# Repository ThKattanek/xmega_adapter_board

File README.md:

# XMEGA Adapter Board (ATXMEGA256D3)
Eine Adapter Platine für den XMEGA, um ihn auf dem Steckbrett zu nutzen.

### <font color="red"> Vorsicht! Revision 1.2.1 noch nicht fertigen lassen, bis ich die ersten Platinen getestet habe! </font>

## Fotos

## Anschluss und Programmiergerät

Das Board muss an VCC und AVCC mit 3,3V verbunden werden sowie GND mit Masse.  Ich verwende als Programmieragerät den AVR Programmer von Diamex. (Atmel AVRISP MKII kompatibel)
[https://www.diamex.de/dxshop/Diamex-AVR-Prog-Programmer-fuer-ISP-PDI-TPI](https://www.diamex.de/dxshop/Diamex-AVR-Prog-Programmer-fuer-ISP-PDI-TPI)  
Der XMEGA wird lediglich über 2 Leitungen mit den Programmiergerät verbunden. (PDI_CLK und PDI_DATA) Die Kommunikation erfolgt über PDI.

## Erste Schritte mit AVRDUDE und den XMEGA
### 1. avrdude -c avrispmkII -p x256d3 
Wenn alles richtig angeschlossen wurde sollte als Device ID 0x1e9844 ausgegeben werden.

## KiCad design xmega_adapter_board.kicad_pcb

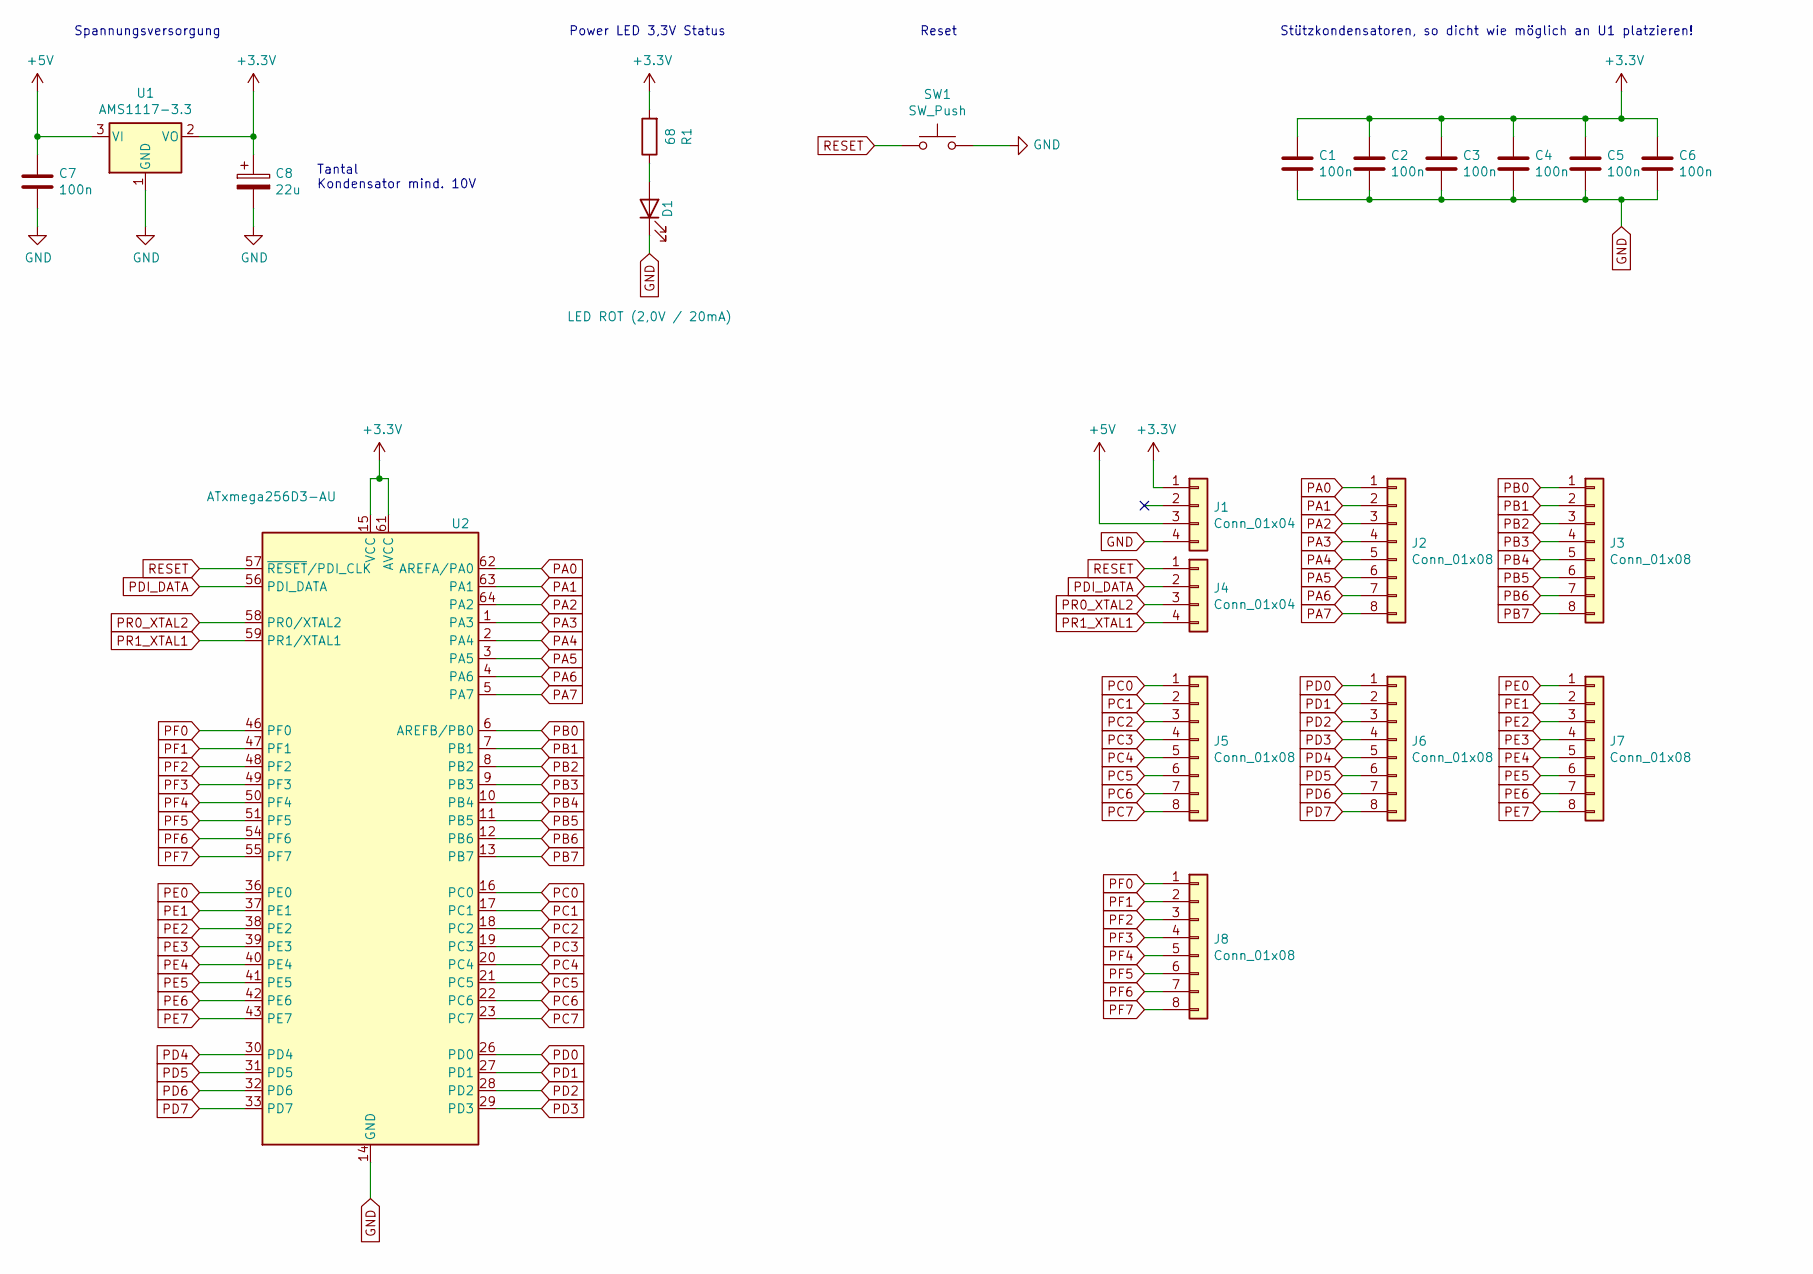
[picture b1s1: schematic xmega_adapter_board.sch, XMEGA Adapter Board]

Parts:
C1, C2, C3, C4, C5, C6, C7: 100n; C_0805_2012Metric_Pad1.18x1.45mm_HandSolder
C8: 22u; CP_EIA-3528-12_Kemet-T_Pad1.50x2.35mm_HandSolder
D1: LED ROT (2,0V / 20mA); LED_0805_2012Metric_Pad1.15x1.40mm_HandSolder
J1, J4: Conn_01x04; PinHeader_1x04_P2.54mm_Vertical
J2, J3, J5, J6, J7, J8: Conn_01x08; PinHeader_1x08_P2.54mm_Vertical
R1: 68; R_0805_2012Metric_Pad1.20x1.40mm_HandSolder
SW1: SW_Push; SW_KMR231G
U1: AMS1117-3.3; SOT-223-3_TabPin2
U2: ATxmega256D3-AU; TQFP-64_14x14mm_P0.8mm

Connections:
+3V3: C1.1, C2.1, C3.1, C4.1, C5.1, C6.1, C8.1, J1.1, R1.2, U1.2 (VO), U2.15 (VCC), U2.25 (VCC), U2.35 (VCC), U2.45 (VCC), U2.53 (VCC), U2.61 (AVCC)
+5V: C7.1, J1.3, U1.3 (VI)
GND: C1.2, C2.2, C3.2, C4.2, C5.2, C6.2, C7.2, C8.2, D1.1 (K), J1.4, SW1.2, U1.1 (GND), U2.14 (GND), U2.24 (GND), U2.34 (GND), U2.44 (GND), U2.52 (GND), U2.60 (GND)
unnamed: D1.2 (A), R1.1
PA0: J2.1, U2.62 (AREFA/PA0)
PA1: J2.2, U2.63 (PA1)
PA2: J2.3, U2.64 (PA2)
PA3: J2.4, U2.1 (PA3)
PA4: J2.5, U2.2 (PA4)
PA5: J2.6, U2.3 (PA5)
PA6: J2.7, U2.4 (PA6)
PA7: J2.8, U2.5 (PA7)
PB0: J3.1, U2.6 (AREFB/PB0)
PB1: J3.2, U2.7 (PB1)
PB2: J3.3, U2.8 (PB2)
PB3: J3.4, U2.9 (PB3)
PB4: J3.5, U2.10 (PB4)
PB5: J3.6, U2.11 (PB5)
PB6: J3.7, U2.12 (PB6)
PB7: J3.8, U2.13 (PB7)
PC0: J5.1, U2.16 (PC0)
PC1: J5.2, U2.17 (PC1)
PC2: J5.3, U2.18 (PC2)
PC3: J5.4, U2.19 (PC3)
PC4: J5.5, U2.20 (PC4)
PC5: J5.6, U2.21 (PC5)
PC6: J5.7, U2.22 (PC6)
PC7: J5.8, U2.23 (PC7)
PD0: J6.1, U2.26 (PD0)
PD1: J6.2, U2.27 (PD1)
PD2: J6.3, U2.28 (PD2)
PD3: J6.4, U2.29 (PD3)
PD4: J6.5, U2.30 (PD4)
PD5: J6.6, U2.31 (PD5)
PD6: J6.7, U2.32 (PD6)
PD7: J6.8, U2.33 (PD7)
PDI_DATA: J4.2, U2.56 (PDI_DATA)
PE0: J7.1, U2.36 (PE0)
PE1: J7.2, U2.37 (PE1)
PE2: J7.3, U2.38 (PE2)
PE3: J7.4, U2.39 (PE3)
PE4: J7.5, U2.40 (PE4)
PE5: J7.6, U2.41 (PE5)
PE6: J7.7, U2.42 (PE6)
PE7: J7.8, U2.43 (PE7)
PF0: J8.1, U2.46 (PF0)
PF1: J8.2, U2.47 (PF1)
PF2: J8.3, U2.48 (PF2)
PF3: J8.4, U2.49 (PF3)
PF4: J8.5, U2.50 (PF4)
PF5: J8.6, U2.51 (PF5)
PF6: J8.7, U2.54 (PF6)
PF7: J8.8, U2.55 (PF7)
PR0_XTAL2: J4.3, U2.58 (PR0/XTAL2)
PR1_XTAL1: J4.4, U2.59 (PR1/XTAL1)
RESET: J4.1, SW1.1, U2.57 (~RESET~/PDI_CLK)

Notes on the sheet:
Stützkondensatoren, so dicht wie möglich an U1 platzieren!
Spannungsversorgung
Tantal Kondensator mind. 10V
Power LED 3,3V Status
Reset

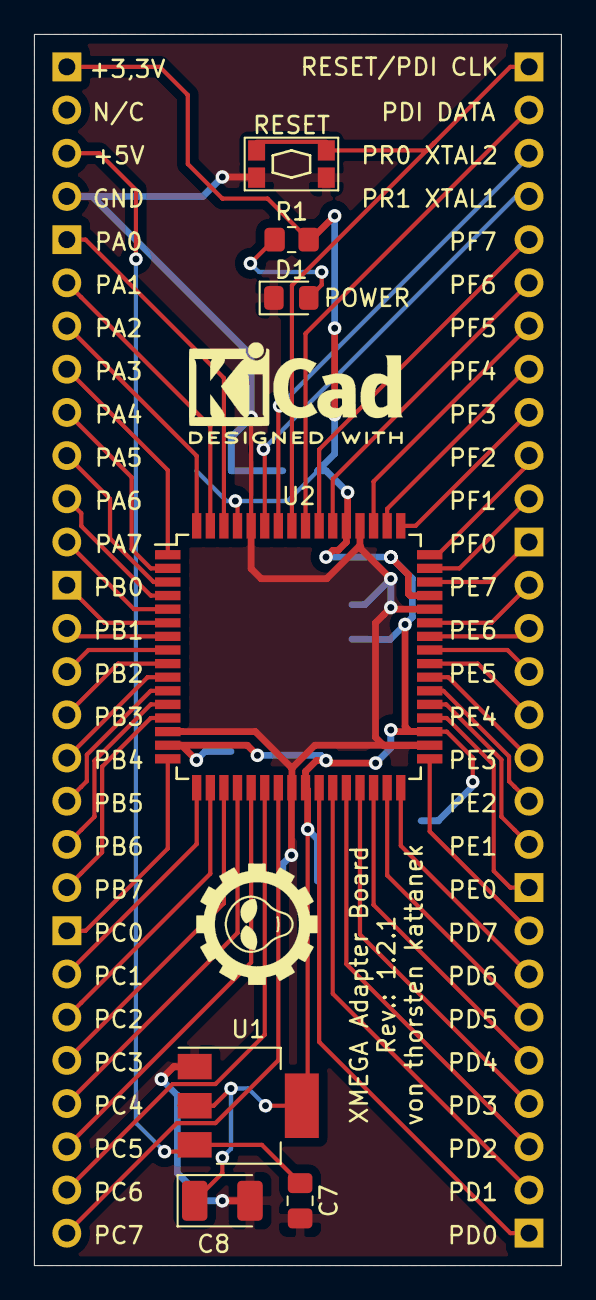
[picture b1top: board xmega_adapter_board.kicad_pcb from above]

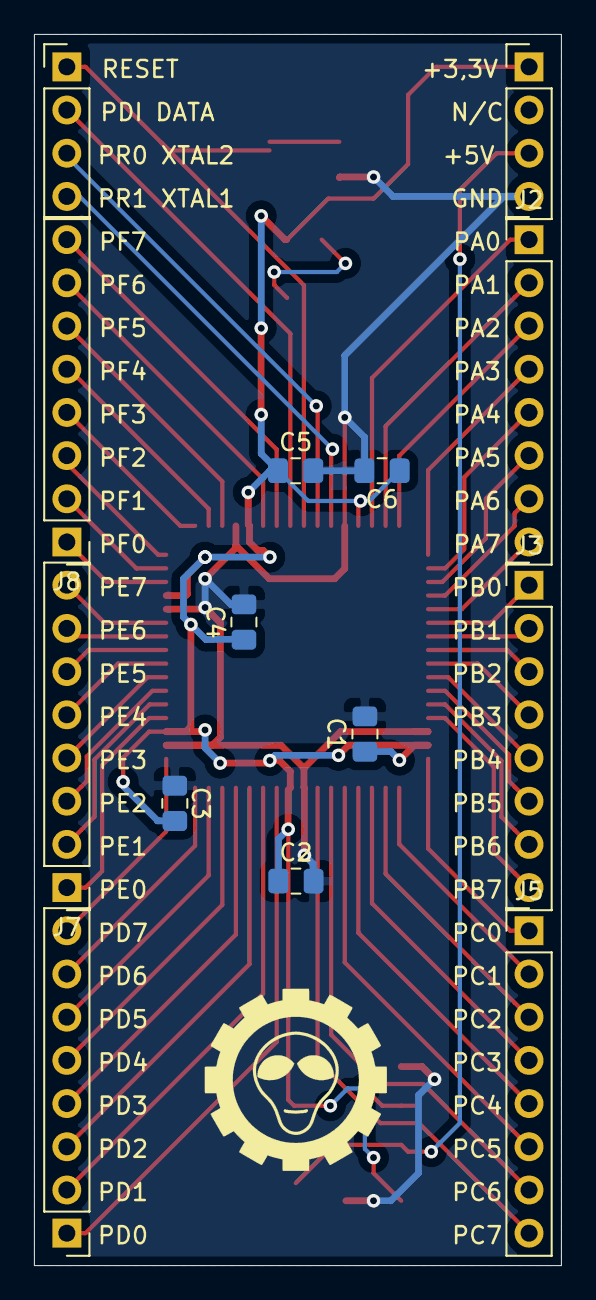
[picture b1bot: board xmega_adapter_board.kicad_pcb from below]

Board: 2 copper layers, 31.0 x 72.4 mm, 21 parts (14 on the bottom side), 56 nets.

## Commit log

2020-06-24 Revision 1.0.0 fertig gestellt.
2020-06-24 Screenshots hinzugefuegt.
2020-06-24 Beschriftung geaendert, borad -> board
2020-06-25 final of revision 1.0.0
2020-06-25 Schematic als PDF erstellt
2020-06-25 added license
2020-07-04 added two real images from this hardware
2020-07-04 readme.md erweitert
2020-07-04 Hello World Example hinzugefuegt
2020-07-04 Alle Bilder im Unterverzeichnis images
2020-07-04 Neues Foto
2020-07-12 Power LED als rote SMD LED hinzugefuegt
2020-10-11 changed board to version 1.1.0 - added a 3.3 voltage regulator and a reset button
2020-10-11 changed to rev 1.2.0
2020-10-12 new bom and gerfiles
2020-10-23 changed -gitignore
2020-10-24 added kicat logo to pcb
